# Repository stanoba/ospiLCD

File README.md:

# ospiLCD

This is OpenSprinkler pi I2C LCD python script which gets data from OpenSprinkler API and sends to I2C LCD.

**features:**
* 16x2 and 20x4 I2C LCDs are supported (PCF8574T based, after some changes MCP23008 is supported too)
* first two lines are identical to LCD on OpenSprinkler 2.x (with icons)
* third and fourth lines are displaying information based on ospi status (remaining watering time, water level in %, E1 stations status)
* LCD backlight is controlled from OpenSprinkler GUI (Brightness = 0 ->> OFF, Brightness > 1 ->> ON)
* LCD is refreshed in one minute interval (can be changed in cron)
* this script in combination with Raspberry pi and I2C LCD can be used as remote OpenSprinkler LCD

Installation instructions
=====

Install RPLCD library directly from [PyPI](https://pypi.python.org/pypi/RPLCD/) using pip:

    $ sudo pip install RPLCD

Intall smbus and i2c tools:

    $ sudo apt-get install python-smbus i2c-tools

Intall ospiLCD script:

    $ cd /home/pi/
    $ wget  https://raw.githubusercontent.com/stanoba/ospiLCD/master/ospiLCD.py
    $ chmod +x ospiLCD.py
    
Solder 2x3 pin header to ospi board:

Remove two 4K7 pull-up resistors from I2C LCD backpack:

Resistors are feeding 5V to Raspberry pi GPIO pins = not safe.

Connect I2C LCD to ospi pin header:

Run I2C scanner to detect all available address:

    $ sudo i2cdetect -y 1

You should see I2C LCD at address 0x27:

Edit parameters (osAddress, osPort, md5hash, LCDcols, LCDrows) according your ospi and LCD in /home/pi/ospiLCD.py:

    $ nano /home/pi/ospiLCD.py

Test the script if is working:

    $ /home/pi/ospiLCD.py

If the script is working without error, schedule it via cron:

    $ crontab -e
    
Add folowing line into cron:

    */1 * * * * python /home/pi/ospiLCD.py
    
Note: Script is executed every minute.

HW - I2C LCD adapter
=====
You can find LCD adapter PCB in HW folder.

PCB can be ordered from [PCBs.io](https://PCBs.io/share/zM39D). ($0.89 / 4pcs)

3D Printed case
=====
STL files:https://www.thingiverse.com/thing:2576148

Output examples:
=====
Blue LCD 16x2:

Green LCD 20x4:

Green LCD 20x4 and ospi with expansion board (E1):

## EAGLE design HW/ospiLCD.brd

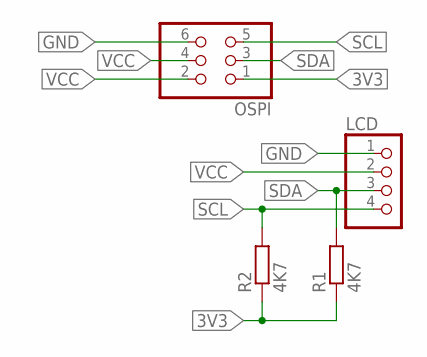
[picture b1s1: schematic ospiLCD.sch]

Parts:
LCD: PINHD-1X4; 1X04
OSPI: PINHD-2X3; 2X03
R1, R2: 4K7; R0603

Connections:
3V3: OSPI.1, R1.1, R2.1
GND: LCD.1, OSPI.6
SCL: LCD.4, OSPI.5, R2.2
SDA: LCD.3, OSPI.3, R1.2
VCC: LCD.2, OSPI.2, OSPI.4

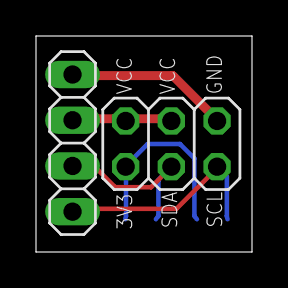
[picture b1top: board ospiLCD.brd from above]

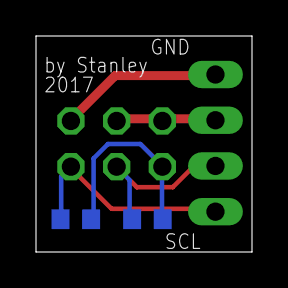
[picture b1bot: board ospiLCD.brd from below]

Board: 2 copper layers, 12.0 x 12.0 mm, 4 parts (2 on the bottom side), 5 nets.

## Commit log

2017-09-02 Initial release
2017-09-02 Rename lcd_ospi.py to ospiLCD.py
2017-09-02 Network detection fix
2017-09-02 Network detection fix 2
2017-09-02 fix default settings
2017-09-02 image upload
2017-09-02 More images
2017-09-02 smaller image
2017-09-03 HW files upload
    Designed PCB in eagle.
2017-09-03 I2C scan image
2017-09-03 PCB and I2C scan info
2017-09-03 main picture
2017-09-06 Code and syntax validation.
2017-09-10 locale settings
    Added new option to set locale according Raspberry pi settings.
2017-10-09 new images
2017-10-09 New images + case
